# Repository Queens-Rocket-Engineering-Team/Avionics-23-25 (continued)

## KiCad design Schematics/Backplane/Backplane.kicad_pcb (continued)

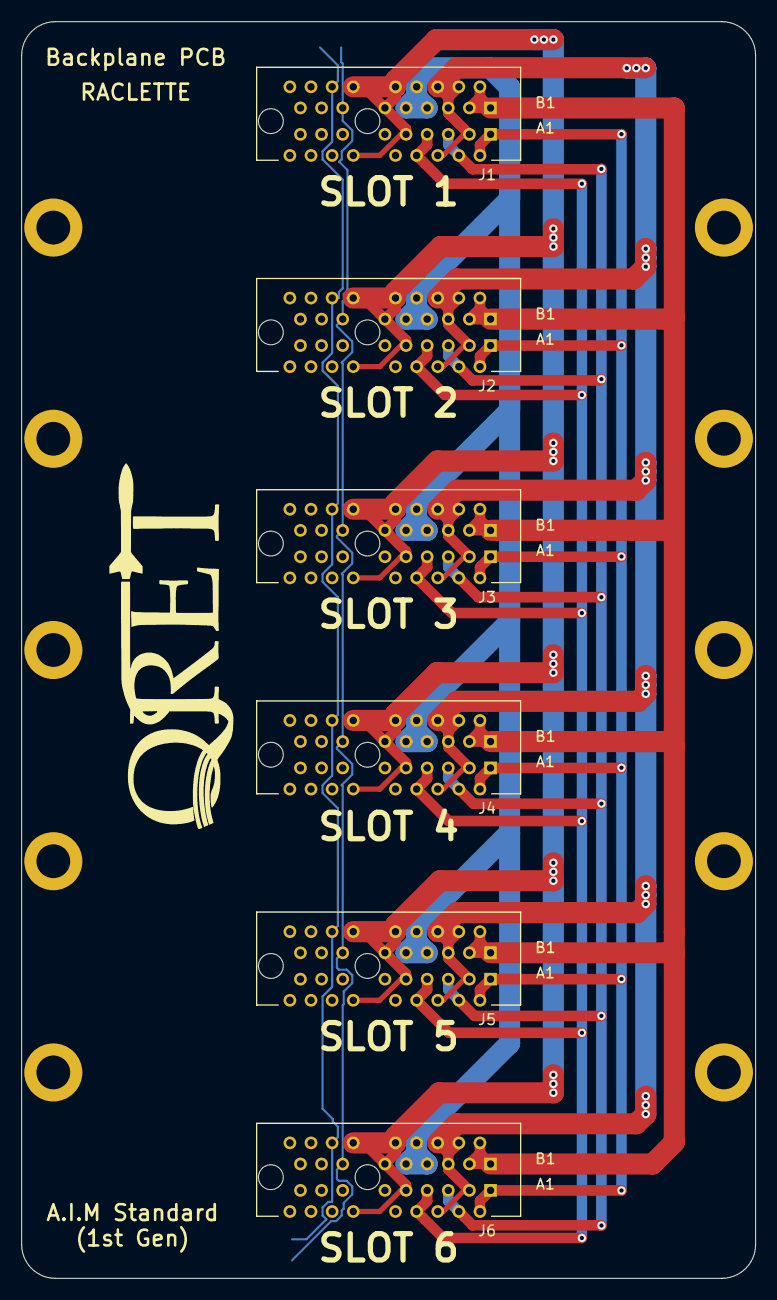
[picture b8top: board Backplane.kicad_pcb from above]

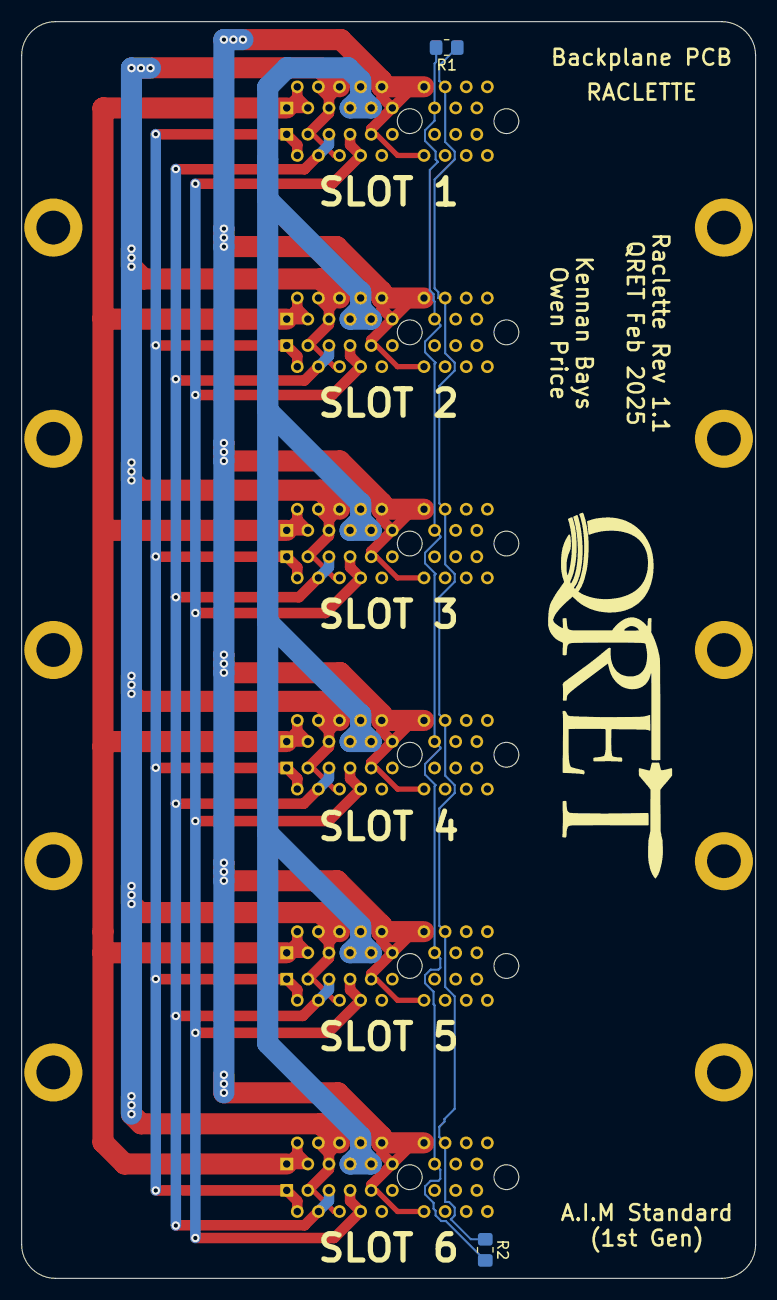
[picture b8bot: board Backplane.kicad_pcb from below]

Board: 2 copper layers, 69.5 x 119.0 mm, 18 parts (2 on the bottom side), 9 nets.

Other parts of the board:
H5, H6, H7, H8, H9, H10: MountingHole; MountingHole_3.2mm_M3_ISO14580_Pad

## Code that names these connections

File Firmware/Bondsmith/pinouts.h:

// Header file that contains all pinouts for Bondsmith
#define BATT1_SENSE_PIN PA0
#define BATT2_SENSE_PIN PA1
#define CURR_SENSE_PIN PA2
#define RAIL_5V_SENSE_PIN PA3
#define PSU_TEMP_PIN PA4
#define RAIL_12V_SENSE_PIN PA5
#define CURR_SENSOR_PWR_PIN PA6
#define BATT1_DISABLE_PIN PA7
#define BATT2_DISABLE_PIN PA8
#define PI_TX_PIN PA9
#define PI_RX_PIN PA10
#define FAN_PWM_PIN PA11
#define FAN_TACH_PIN PA12
#define STATUS_LED_PIN PA15

#define GPIO_PB0_PIN PB0
#define GPIO_PB1_PIN PB1
#define RGB12_B_PIN PB3
#define RGB12_G_PIN PB4
#define RGB12_R_PIN PB5
#define LID_SENSE_PIN PB6
#define BUTT3_SENSE_PIN PB7
#define BUTT2_SENSE_PIN PB8
#define BUTT1_SENSE_PIN PB9
#define GPIO_SCL_PIN PB10
#define GPIO_SDA_PIN PB11
#define AUX_PWR_ENABLE_PIN PB13
#define RGB_DATA_PIN PB14
#define VRX_PWR_ENABLE_PIN PB15

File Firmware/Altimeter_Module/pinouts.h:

// Header file that contains all pinouts for this module
#define BATT_SENSE_PIN PB0
#define CURR_SENSE_PIN PB1
#define RGB_DATA_PIN PB3
#define ACCEL_INT1_PIN PB5
#define ACCEL_INT2_PIN PB6
#define GYRO_INT_PIN PB7
#define CAN_RX_PIN PB8
#define CAN_TX_PIN PB9
#define SCL_PIN PB10
#define SDA_PIN PB11
#define FLASH_CS_PIN PB12
#define FLASH_SCK_PIN PB13
#define FLASH_MISO_PIN PB14
#define FLASH_MOSI_PIN PB15

#define FIRE_DROGUE_PIN PA1
#define CONT_DROGUE_PIN PA2
#define FIRE_MAIN_PIN PA3
#define CONT_MAIN_PIN PA4
#define FLASH_RESET_PIN PA8
#define BUZZER_PIN PA9
#define USB_DM_PIN PA11
#define USB_DP_PIN PA12
#define STATUS_LED PA15

#define MS5607_ADDR 0x76
#define MPU6050_ADDR 0x69
#define QMA6100_ADDR 0x13

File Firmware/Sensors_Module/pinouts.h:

// Header file that contains all pinouts for this module
#define CAMERA_POWER_PIN PB0
#define CURR_SENSE_PIN PB1
#define RGB_DATA_PIN PB3
#define CAN_RX_PIN PB8
#define CAN_TX_PIN PB9
#define SCL_PIN PB10
#define SDA_PIN PB11
#define FLASH_CS_PIN PB12
#define FLASH_SCK_PIN PB13
#define FLASH_MISO_PIN PB14
#define FLASH_MOSI_PIN PB15

#define USB_TX_PIN PA2
#define USB_RX_PIN PA3
#define BUZZER_PIN PA7
#define FLASH_RESET_PIN PA8
#define CAMERA_TX_PIN PA9
#define CAMERA_RX_PIN PA10
#define CAMERA_PWM_PIN PA11
#define STATUS_LED_PIN PA15

#define MAGN_ADDR 0x0E 
#define BME680_ADDR 0x77

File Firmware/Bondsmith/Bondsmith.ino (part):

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 * 
 * KNOWN HARDWARE PROBLEMS:
 * - The resistor dividers for the 5V and 12V rail monitoring need a bypass capacitor as the divider is too high impedance. Workaround was longer ADC sampling time.
 * - The "BATT1_EN" and "BATT2_EN" signals exposed for LED indicators is inverted (HIGH disables a battery), thus the LEDs are inverted. Swap the GND pin to 3.3V to fix.
  */


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movingAvg batt2RawFilter(20);
movingAvg currentRawFilter(20);

Adafruit_NeoPixel indicators(NUM_RGB_LEDS, RGB_DATA_PIN, NEO_GRB + NEO_KHZ800);

/*
 * Reads internal voltage reference and back-calculates
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  // Configure pinmodes
  pinMode(BATT1_SENSE_PIN, INPUT);
  pinMode(BATT2_SENSE_PIN, INPUT);
  pinMode(CURR_SENSE_PIN, INPUT);
  pinMode(RAIL_5V_SENSE_PIN, INPUT);
  pinMode(PSU_TEMP_PIN, INPUT);
  pinMode(RAIL_12V_SENSE_PIN, INPUT);
  pinMode(CURR_SENSOR_PWR_PIN, OUTPUT);
  pinMode(BATT1_DISABLE_PIN, OUTPUT);
  pinMode(BATT2_DISABLE_PIN, OUTPUT);
  pinMode(FAN_PWM_PIN, OUTPUT);
  pinMode(FAN_TACH_PIN, INPUT);
  pinMode(STATUS_LED_PIN, OUTPUT);
  pinMode(RGB12_B_PIN, OUTPUT);
  pinMode(RGB12_G_PIN, OUTPUT);
  pinMode(RGB12_R_PIN, OUTPUT);
  pinMode(LID_SENSE_PIN, INPUT);
  pinMode(BUTT3_SENSE_PIN, INPUT);
  pinMode(BUTT2_SENSE_PIN, INPUT);
  pinMode(BUTT1_SENSE_PIN, INPUT);
  pinMode(AUX_PWR_ENABLE_PIN, OUTPUT);
  pinMode(RGB_DATA_PIN, OUTPUT);
  pinMode(VRX_PWR_ENABLE_PIN, OUTPUT);

  // Immediately switch to the higher-voltage battery (TODO: IMPLEMENT)
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  digitalWrite(BATT2_DISABLE_PIN, LOW);

  // Config fan tach interrupt
  attachInterrupt(digitalPinToInterrupt(FAN_TACH_PIN), onFanTach, FALLING);

  // Turn on VRX and AUX ports
  digitalWrite(AUX_PWR_ENABLE_PIN, HIGH);
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  // Query analog sensors
  uint16_t batt1Raw = batt1RawFilter.reading(analogRead(BATT1_SENSE_PIN));
  uint16_t batt2Raw = batt2RawFilter.reading(analogRead(BATT2_SENSE_PIN));
  uint16_t currRaw = currentRawFilter.reading(analogRead(CURR_SENSE_PIN));
  uint16_t rail5Raw = rail5RawFilter.reading(analogRead(RAIL_5V_SENSE_PIN));
  uint16_t rail12Raw = rail12RawFilter.reading(analogRead(RAIL_12V_SENSE_PIN));
  uint16_t psuTempRaw = analogRead(PSU_TEMP_PIN);
  // Query lid sensor & buttons
  bool lidClosed = digitalRead(LID_SENSE_PIN)==LOW;
  bool b1Down = digitalRead(BUTT1_SENSE_PIN)==LOW;
  bool b2Down = digitalRead(BUTT2_SENSE_PIN)==LOW;
  bool b3Down = digitalRead(BUTT3_SENSE_PIN)==LOW;
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// Sets the current cooling fan(s) power
void setFanPower(uint8_t pwr) {
  curFanPower = pwr;
  analogWrite(FAN_PWM_PIN, pwr);
}//setFanPower()


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
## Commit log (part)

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2025-06-07 added logo
2025-06-07 added video output folder
2025-06-07 added camera status check
2025-06-07 remove loop for performance
2025-06-11 Removed fan curve, just runs at 100% now
2025-06-12 COMPILED CURRENT CODE TO BINARY FILE
2025-06-12 Now just communicate altitude as whole number & COMPILED BINARY
    Not as accurate but so much simpler. me so tired.
2025-06-12 increase baud rate & COMPILED BINARY
2025-06-12 Fixed bug where flash would just erase on startup & COMPILED BINARY
2025-08-29 Rough draft minus things I need to ask about
2025-08-29 Cleaned up schematic
2025-08-29 Getting close to a rough schematic
2025-08-29 Minor Adjustments
    - Adjusted LED resistor values
    - Cleaned up PCB project lightly
2025-08-29 Reorganized schematic, added attribution, adjusted parts
2025-08-29 First draft of layout finished, all DRC passed
2025-08-29 Best attempt at 2-layer PCB (incomplete)
2025-08-29 Created KiCAD Project
2025-08-29 Added footprints
    Added footprints
2025-08-29 Sourced datasheets, symbols, and footprints for all parts on list. Added all relevant symbols to schematic for the most part.
2025-08-29 Added LCSC part numbers
    Added LCSC part numbers
2025-08-29 Finalized Schematic
2025-08-29 Selected inductors & capacitors
2025-08-29 Added part numbers, finalized PCB layout
2025-08-29 Updated branch name to reflect my work will be in here too, formatted communications schematic/layout pages, integrated already created subcircuit schematics into communications schematic, and added 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
2025-08-29 All values displayed
2025-08-29 Cleaning up schematic
2025-08-29 Progress 01/27 5PM
    - Added Accelerometer and Pressure sensor + pull up resistors for I2C
    - Included repeated (WIP) subcircuits from other modules eg. CANBUS, current sensing
2025-08-29 Added antenna Digikey part number & 3D model
2025-08-29 Very minor PCB tweaks
2025-08-29 Various Revisions
    -Added footprints and 3D models
    -Also adjusted RFM95 pinouts
    -Added more LCSC part numbers
2025-08-29 Various Small Updates
    - Switched US resistor symbols to standard ones
    - Added more RGB LEDs
    - Added battery measurement circuit
    - Connected edge connector properly
    - Rearranged various components
2025-08-29 Added last few sub-circuits (buzzer, SWD), connected a bunch of pins between modules and STM, changed ideal diode circuit. Overall, rough draft minus edge connector
2025-08-29 small changes
2025-08-29 Updated symbols for electrolytic capacitors
2025-08-29 Updated some digikey part numbers
2025-08-29 Updated stack edge connector (V1)
2025-08-29 PCB layout tweaks & Silkscreen added
2025-08-29 Layout done except antenna trace
2025-08-29 Updated PCB "Copper to edge clearance" to 0.3mm
    PCB needs updating accordingly
2025-08-29 Schematic adjustments for USB-C
2025-08-29 50 ohm characterstic impedance antenna trace?:
2025-08-29 Adjusted part nnumbers + ERC pass
2025-08-29 Ground net routed w/ vias
2025-08-29 Updated layout to pass DRC with new copper-edge clearance
2025-08-29 Layout updated accordingly, DRC mostly done (some silk screen overlap)
2025-08-29 Added type-C connector + tweaked PCB layout (DRC pass)
2025-08-29 Added custom edge connector symbol to project
2025-08-29 2/20 6:30
    removed extra symbol
2025-08-29 3:24
2025-08-29 update 5:07 2/29
    buzzer
2025-08-29 Added E-Match fire & continuity circuit
2025-08-29 Update Altimeter_Module.kicad_sch
    new revision
2025-08-29 Updated STM32 pinout
2025-08-29 Switched to using secondary channel power rails
    Was previously just using the primary rails. Altimeter should be using the secondary rails (for isolation + redundancy)
2025-08-29 progress 6:35 2/29
    added rgb leds
2025-08-29 Fixed pressure sensor & accelerometer
2025-08-29 Rebase to orgin/main
2025-08-29 Updated MS5607 footprint + added many 3D models
2025-08-29 progress 12:30 3/14
    very very rough work
2025-08-29 progress 12:00 3/15
2025-08-29 Reset PCB layout
2025-08-29 Preliminary PCB layout (DRC passes)
2025-08-29 Silkscreen adjustments
2025-08-29 added proccessor and added sam-m10q symbol
2025-08-29 added schematics
2025-08-29 added footprints and symbols
2025-08-29 added notes
2025-08-29 added ideal diodes and renamed GPS labels
2025-08-29 added note to JST connecter
2025-08-29 finished daughter board waiting for approval
2025-08-29 added footprints from comm board
2025-08-29 Verified part numbers & made ERC pass
    Also cleaned up unnecessary footprints & added bulk filtering capacitor to GPS antenna board
2025-08-29 Changed buttons from PTS636 to TS1187A
2025-08-29 Added digikey & LCSC part numbers to symbols
2025-08-29 starting daughter board PCB layout
2025-08-29 Updated various capacitors
2025-08-29 finished PCB routing, waitting for approval
2025-08-29 Fixed voltage divider on buzzer circuit
2025-08-29 Revert "starting PCB layout"
    This reverts commit 0f9aa6cd92282e41b038e1a8acfc0611b64ad155.
2025-08-29 start pin assignments
2025-08-29 gps daughter board GND stiching
2025-08-29 added LCSC & FPs to LEDs, Diodes, Rs, & Caps
2025-08-29 Cleaned up GPS antenna schematic
2025-08-29 Add silkscreen & final PCB adjustments
2025-08-29 deleted more uneeded files
2025-08-29 Add tentative edge connector
2025-08-29 updates from comm schemat and layout update
2025-08-29 Added mounting holes to GPS antenna board
2025-08-29 moved GPS daughter board to seperate project
2025-08-29 Needs Review but mostly done apart from a few pins on the MCU
2025-08-29 started PCB layout
2025-08-29 Added logging function to the GPS
2025-08-29 Enable CANBUS in extra conf
2025-08-29 Add Kuhglocke firmware
2025-08-29 Added Canbus Status Check for Sensors Module
2025-08-29 Updated Authors
2025-08-29 Define HSE crystal
2025-08-29 Deployed sensors code
    Note that the flash table size is known to cause problems, and the incorrect camera power pin is used. This code needs some work, BUT its what flew at SPAC24.
2025-08-29 Fixed camera pin & started using pinouts def file
2025-08-29 Enabled debug mode for GPS and fixed errors
2025-08-29 Fixed bugs in flash table
2025-08-29 Made templates for pinout files
2025-08-29 Added note about Accelerometer change
2025-08-29 Version bump
2025-08-29 Fixed GPS so old connection doesn't count as a fix
2025-08-29 Cleaned up & documented code
    Also started using the pinouts file
2025-08-29 Fixed incorrect pinout for BM1422AGMV (Rev 1.0A)
2025-08-29 Updated Start Up Buzzer
2025-08-29 Various changes
    -Added many symbols and footprints
    -Pulled base changes from other schematics
    -Organized schematic
    -Added attribution text
2025-08-29 Final tweaks
2025-08-29 Fixed altimeter drogue deployment, added main deployment
2025-08-29 Fixed data logging bug & cleaned up MDE
2025-08-29 updates to submodule final attempt at getting accurate data.
2025-08-29 Fixed supercap charger RCB
    Previous use of LM66100 ideal diode didn't work as, when power was lost, the ideal diode would stop functioning properly and would still let power through. Have swapped to a simple 1N5819 Schottky di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
    Also broke out the TX/RX pins of the GPS for easier external programming, if needed.
2025-08-29 Added 6th module slot to schematic
2025-08-29 new changes to submodule
2025-08-29 Ignore VSCode config files
2025-08-29 updated const gravity measurment
2025-08-29 Updated Logic for Altimeter
2025-08-29 Revision bump to V2.0
    Changed to V2.0 due to significant hardware changes
2025-08-29 updates to QMA6100P submodule fully working just needs tuning.
2025-08-29 renamed filed
2025-08-29 Added 3D model for battery/switch connectors
2025-08-29 change library name
2025-08-29 fixed include statement
2025-08-29 fixed basic read MPU6050
2025-08-29 Add kuhglocke kicad project
2025-08-29 Added MCUs + sensors to schematic
2025-08-29 added c++ kalman filter testing for use without a arduino
2025-08-29 create kalman filter simulation arduino script
    relatively small implmentation of a kalman filter for filtering pressure and accelteromter data to measure altiude accuretly
2025-08-29 Completed schematic
2025-08-29 Replaced "LCSC" fields with "JLCPCB" fields
2025-08-29 Bump revision number to V2.0 & V1.2
    GPS module is V2.0, Antenna PCB is V1.2
2025-08-29 Changed SWD programming header to SMD version
2025-08-29 Several schematic improvements
    - Removed initial redundant reverse-polarity-protection and added clamping diodes for affected ADC inputs (should reduce cost & part count)
    - Updated contributor list
    - Added missing part numbers
    - Added switched 12V AUX output
    - Added lid sensor input
    - Changed some connectors to be smaller
2025-08-29 Finalized PCB layout
2025-08-29 Added "PB-FREE" silkscreen to GPS antenna PCB
2025-08-29 Revised PCB layout of GPS Antenna PCB
    The main change was adding the new connector, as well as re-arranging the TX/RX breakout pads
2025-08-29 Added polarity markings to switch connectors
2025-08-29 Initial project files
2025-08-29 Tweaked silkscreen
2025-08-29 Fixed power LED voltage sources
    5V and 12V LEDs were connected to 3.3V. Thanks Teighin :)
2025-08-29 Removed ACS70331 current sensor
2025-08-29 Migrate to KiCAD 7
2025-08-29 Completed PCB layout
    Wow that was disgusting
2025-08-29 Finished schematic
    -Added ADS1256 ADCs
    -Added analog voltage systems
    -Added wheatstone bridge strain gauge circuits
    -Added connectors
    -Adjusted pinout
2025-08-29 Design version bump to V1.1
2025-08-29 Updated the Camera Module
    -connect the thermistor vdiv (V_THERM) to the microcontroller (analog pin)
    -add the correct battery connector for the VTX battery (Mate-n-lok, same as on power module / altimeter)
    - plus an extra connector for the screw switch,
    -connect the VTX control mosfet to the microcontroller
    - change the CP2102's reset resistor (R25) to be a pull UP rather than a pull DOWN
    -replace the 3-pin pin headers with a proper screw terminal.
2025-08-29 Swapped SWD connector to SMD version
2025-08-29 Reduced power LED brightness (3.3k resistor)
2025-08-29 Final silkscreen tweaks
2025-08-29 Removed old project files
2025-08-29 Added Camera Module Layout
2025-08-29 Updated Live Camera Circuit
2025-08-29 Removed current sensor + reduced PWR LED brightness
2025-08-29 Live Camera Base
    The Live Camera Base
2025-08-29 Added power MUX for 5V system
    This is to allow the LoRa1262F30 to operate while running only on 5V USB power, allowing for much easier debugging.
2025-08-29 Replaced LoRa radio with upgraded module
    Replaced RFM65W radio (0.1W) with a LoRa1262F30 radio (1.0W) to schematic
2025-08-29 Added CP2102 USB bridge
    Also bumped version up to V2.0 now that significant hardware changes (e.g. pinout changes) have been made. This breaks firmware backwards compatibility, and thus warrants a major version bump.
2025-08-29 Replaced all "LCSC" fields with "JLCPCB" fields
2025-08-29 Changed all "LCSC" fields to "JLCPCB"
2025-08-29 Tweaks + 3D model additions
    Added/tweaked some notes in the schematic, adjusted silkscreen on PCB + added "PB-FREE" label, updated SWD footprint, and added all missing 3D models to project.
2025-08-29 Tweaked attribution silkscreen
2025-08-29 Added revised buzzer circuit
2025-08-29 Removed current sensor
2025-08-29 Removed legacy RunCam6 PWM output
    Also combined all RunCam6 interface pins to a single terminal block
2025-10-22 Added Manual Camera Project
2025-11-27 organize small backplane
